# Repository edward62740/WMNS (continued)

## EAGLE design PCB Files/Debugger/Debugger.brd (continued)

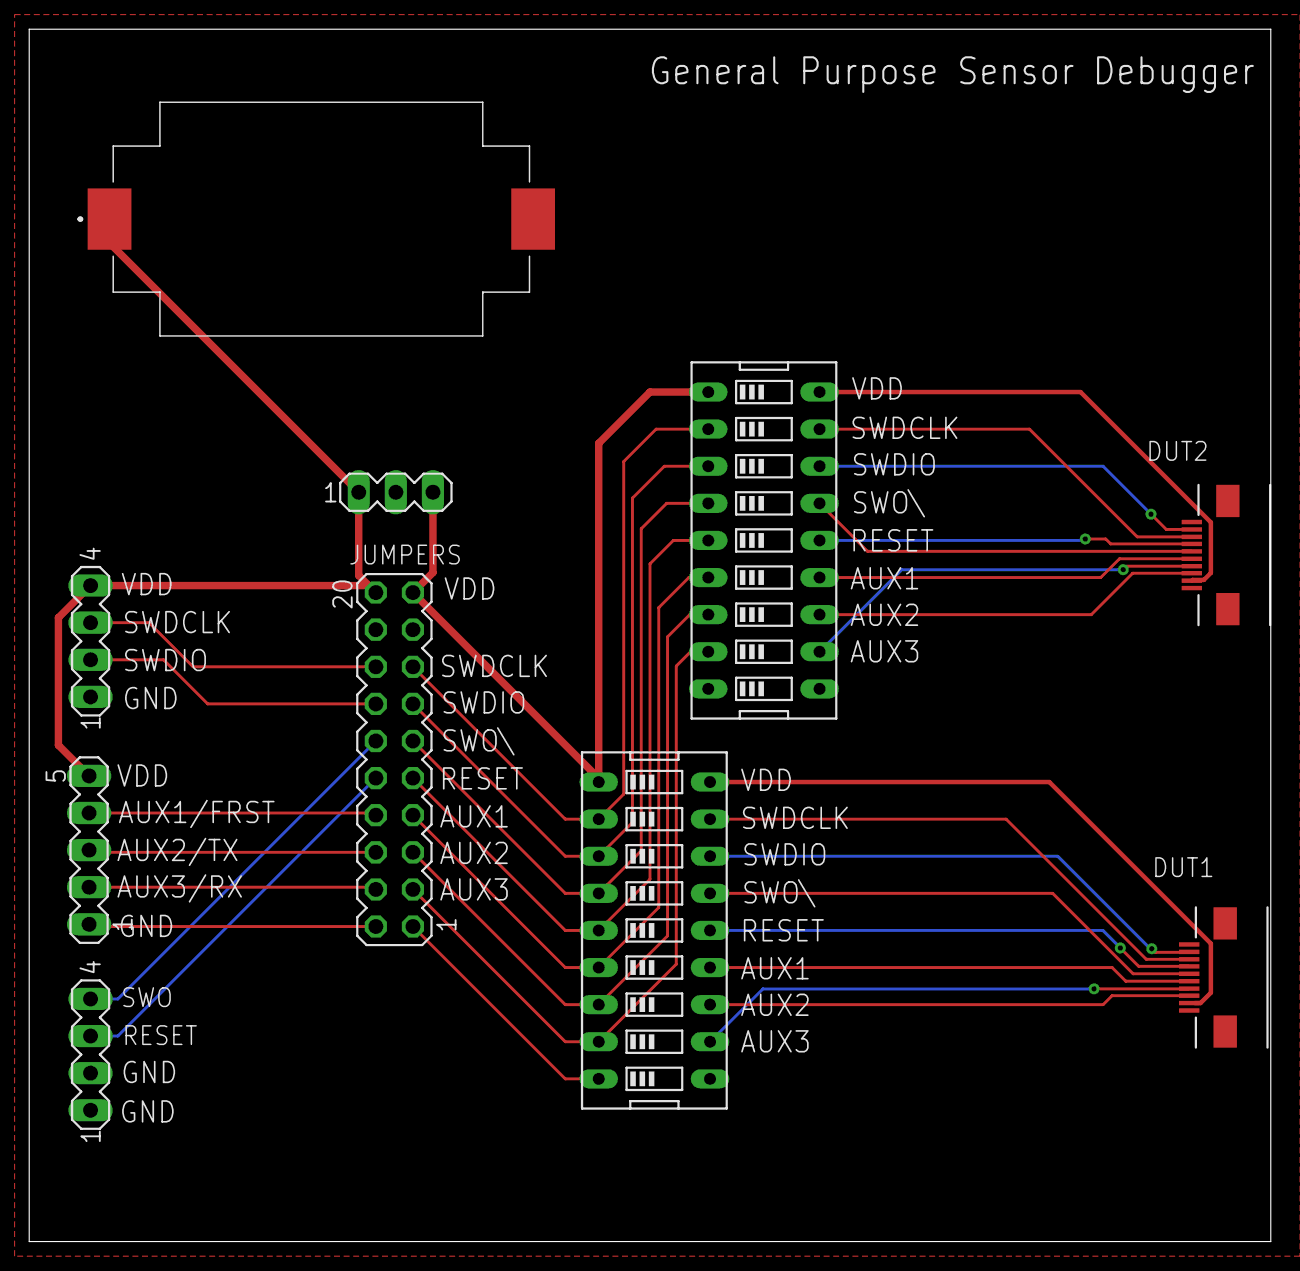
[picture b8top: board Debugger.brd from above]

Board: 2 copper layers, 85.0 x 83.0 mm, 10 parts (0 on the bottom side), 33 nets.

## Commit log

2021-09-19 Updated with v3.0.0 (DEPLOYED)
2021-09-19 Create LICENSE
2022-01-03 Final Deployment
2022-07-01 Updated readme.md to standardize format
